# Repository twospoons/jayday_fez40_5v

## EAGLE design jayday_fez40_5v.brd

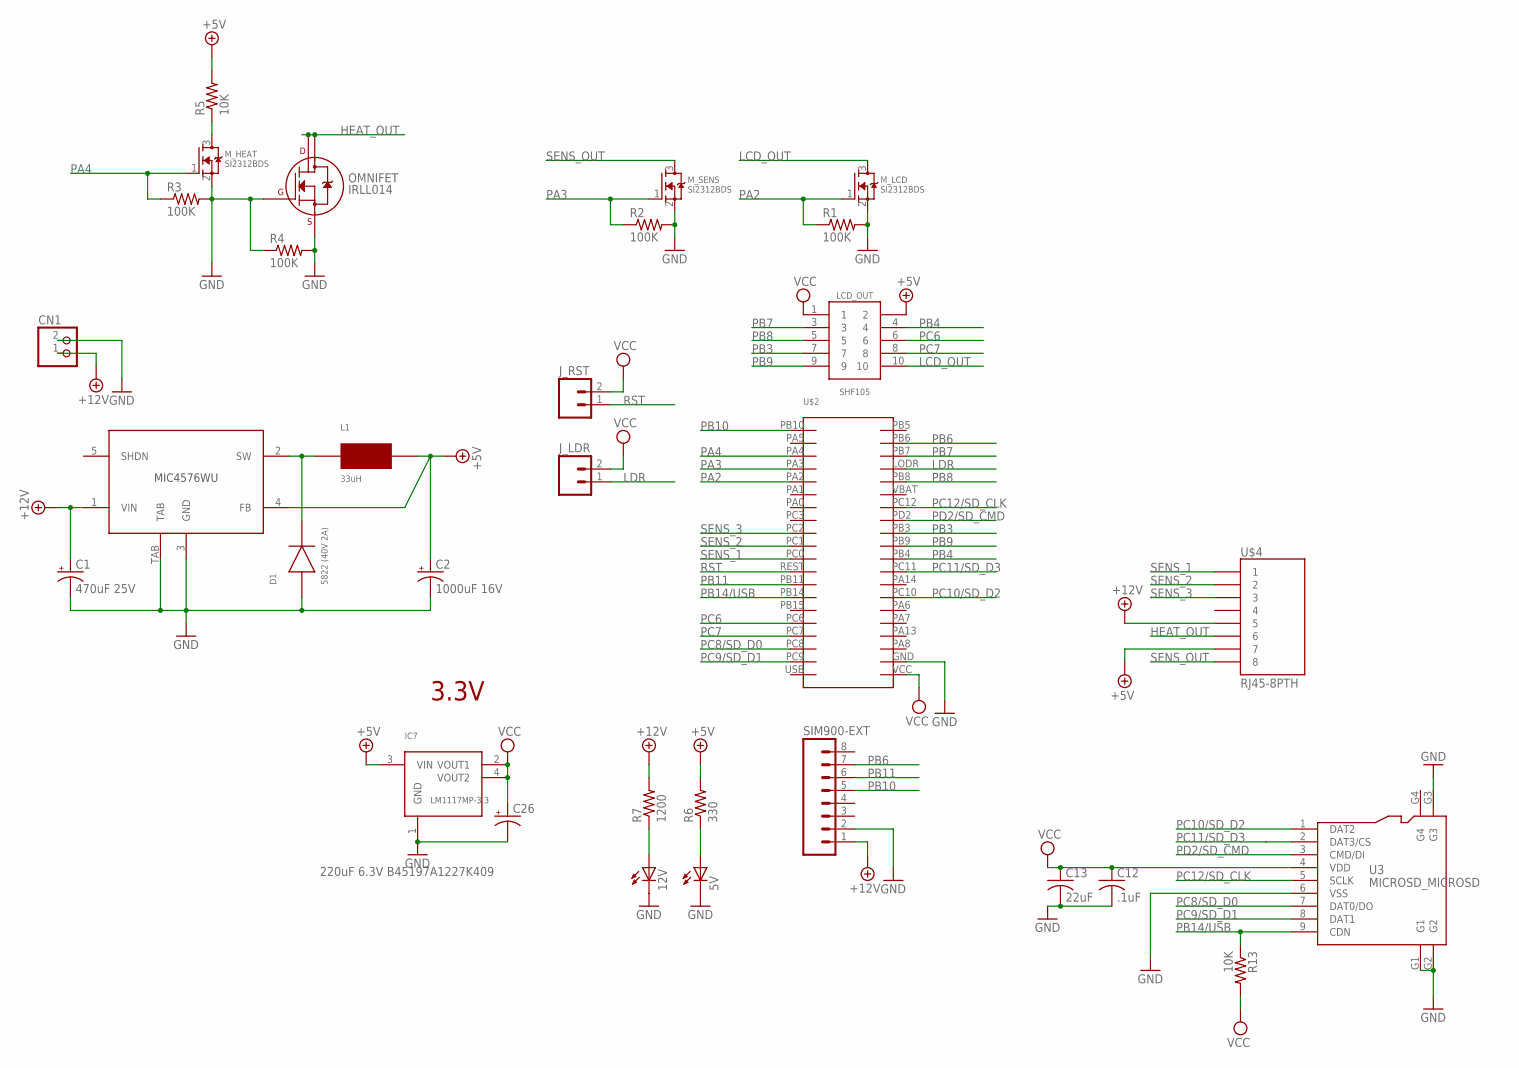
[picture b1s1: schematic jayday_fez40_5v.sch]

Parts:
5V, 12V: LEDCHIPLED_0805; CHIPLED_0805
C1: 470uF 25V; PANASONIC_E
C2: 1000uF 16V; PANASONIC_E
C12: .1uF; C0603K
C13: 22uF; C0805K
C26: 220uF 6.3V B45197A1227K409; D/7343-31W
CN1: JST_2PIN-THM-RA; JST-PH-2-THM-RA
D1: 5822 (40V 2A); GHI_DIODE_SMA
IC7: LM1117MP-3.3; SOT223
J_LDR: M02PTH; 1X02
J_RST: M02PTH; 1X02
L1: 33uH; GHI_UP2BXXX
LCD_OUT: SHF105; GAD_PAC_SMD
M_HEAT: SI2312BDS; TO-236
M_LCD: SI2312BDS; TO-236
M_SENS: SI2312BDS; TO-236
OMNIFET: IRLL014; SOT-223
R1, R2, R3, R4: 100K; R0603
R5, R13: 10K; R0603
R6: 330; R0603
R7: 1200; R0603
SIM900-EXT: M081X08; 1X08
U3: MICROSD_MICROSD
U$1: MIC4576WU; TO263-5
U$2: FEZ_CERB_40
U$4: RJ45-8PTH; RJ45-8

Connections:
+5V: C2.+, IC7.3 (VIN), L1.P$2 (2), LCD_OUT.2, R5.2, R6.2, U$1.4 (FB), U$4.7
+12V: C1.+, CN1.1 (2), R7.2, SIM900-EXT.1, U$1.1 (VIN), U$4.5
GND: 5V.C, 12V.C, C1.-, C2.-, C12.2, C13.2, C26.-, CN1.2 (1), D1.A, IC7.1 (GND), M_HEAT.2 (S), M_LCD.2 (S), M_SENS.2 (S), OMNIFET.1 (G), OMNIFET.3 (S), R1.2, R2.2, R3.2, R4.1, R4.2, SIM900-EXT.2, U3.6 (VSS), U3.G1, U3.G2, U3.G3, U$1.3 (GND), U$1.TAB, U$2.GND
HEAT_OUT: OMNIFET.2 (D1), OMNIFET.4 (D2), U$4.6
LCD_OUT: LCD_OUT.10, M_LCD.3 (D)
LDR: J_LDR.1, U$2.LODR
unnamed: D1.K, L1.P$1 (1), U$1.2 (SW)
unnamed: 5V.A, R6.1
unnamed: M_HEAT.3 (D), R5.1
unnamed: 12V.A, R7.1
PA2: M_LCD.1 (G), R1.1, U$2.PA2
PA3: M_SENS.1 (G), R2.1, U$2.PA3
PA4: M_HEAT.1 (G), R3.1, U$2.PA4
PB3: LCD_OUT.7, U$2.PB3
PB4: LCD_OUT.4, U$2.PB4
PB6: SIM900-EXT.7, U$2.PB6
PB7: LCD_OUT.3, U$2.PB7
PB8: LCD_OUT.5, U$2.PB8
PB9: LCD_OUT.9, U$2.PB9
PB10: SIM900-EXT.5, U$2.PB10
PB11: SIM900-EXT.6, U$2.PB11
PB14/USB: R13.1, U3.9 (CDN), U$2.PB14
PC6: LCD_OUT.6, U$2.PC6
PC7: LCD_OUT.8, U$2.PC7
PC8/SD_D0: U3.7 (DAT0/DO), U$2.PC8
PC9/SD_D1: U3.8 (DAT1), U$2.PC9
PC10/SD_D2: U3.1 (DAT2), U$2.PC10
PC11/SD_D3: U3.2 (DAT3/CS), U$2.PC11
PC12/SD_CLK: U3.5 (SCLK), U$2.PC12
PD2/SD_CMD: U3.3 (CMD/DI), U$2.PD2
RST: J_RST.1, U$2.REST
SENS_1: U$2.PC0, U$4.1
SENS_2: U$2.PC1, U$4.2
SENS_3: U$2.PC2, U$4.3
SENS_OUT: M_SENS.3 (D), U$4.8
VCC: C12.1, C13.1, C26.+, IC7.2 (VOUT1), IC7.4 (VOUT2), J_LDR.2, J_RST.2, LCD_OUT.1, R13.2, U3.4 (VDD), U$2.VCC

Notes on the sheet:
3.3V

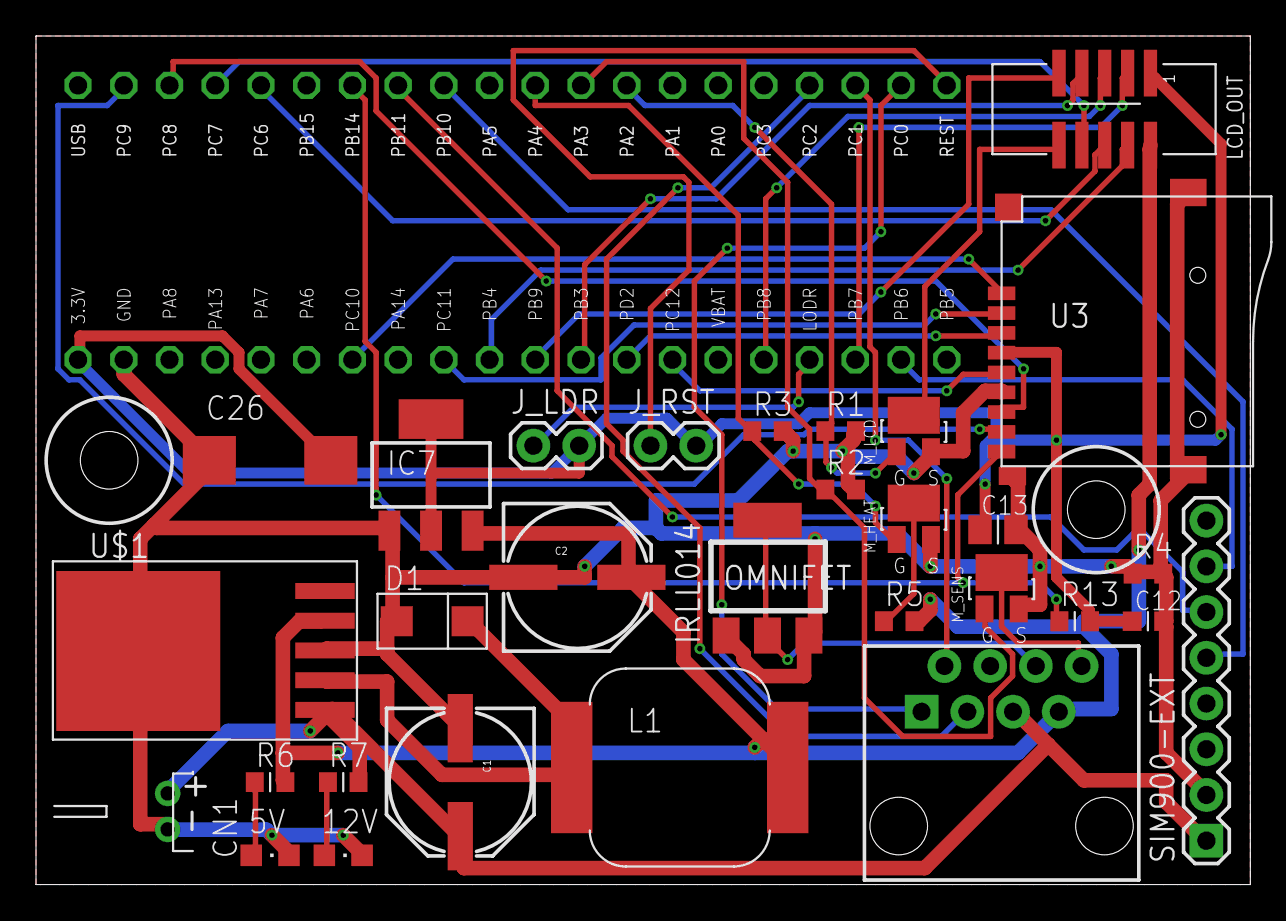
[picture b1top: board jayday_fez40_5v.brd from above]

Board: 2 copper layers, 67.5 x 47.1 mm, 33 parts (0 on the bottom side), 36 nets.

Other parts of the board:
U$3, U$8: HOLE3.2

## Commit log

2012-11-04 FEZ 40 with 5v/3v3

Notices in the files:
parts and their libraries:
SparkFun-Passives: Licensing: CC v3.0 Share-Alike You are welcome to use this library for commercial purposes.
